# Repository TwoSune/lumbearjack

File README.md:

# Lumbearjack - Ortholinear 60% PCB based on Lumberjack by peej

Lumbearjack is a revision of peej's lumberjack with the following features:
* Pro Micro style controller support
* Per-key RGB and Backlight support
* Rotary encoder support
* SMD diode support
* BSS138 logic level shifter

Lumbearjack is currently designed for the following development boards:
* Helios
* Sea Picro
* Frood
* KB2040 (no encoder support)
  
With support for the following, but you may struggle with external USB data lines
* Liatris
* Elite-Pi

At its core, Lumbearjack remains easy to build with minimal soldering experience, but being familiar with soldering is highly recommended for per-key RGB (SK68XX Mini-E) and backlight (WS2812B 2020).

# Ordering parts

See the [Bill of materials](BOM.md) for a detailed list of the required parts.

PCBs can be manufactuered by a variety of online PCB fabricators. You can use [PCBShopper](https://pcbshopper.com/) to search for the best price.

The [zip file in the gerber directory](https://github.com/peej/lumberjack-keyboard/blob/master/gerber/lumberjack.zip) contains the gerber files your fabricator will need to make the PCB.

When uploading the gerber zip files, use the default PCB settings.

If you want to use a plate, there are [gerbers for FR4 plates](https://github.com/peej/lumberjack-keyboard/tree/smd-usbc/plates/gerbers). For the split plate, you will need two plates, one for each half of the keyboard.

# Construction

First, solder all the diodes on the top of the board. If you do not plan on using an encoder or a switch in the middle, you may omit the diode in the center of the board.
After you solder the diodes, solder the USB port on your board. From there, you may decide whether you would like to solder the LEDs or the controller to your board. It is recommended to solder the controller first so you may test your RGB as you solder them a few at a time.

See [the build guide](guide.md) for more information.

## Need help?

Feel free to create an issue request or contact me via discord at xsune for help!

# Firmware

Firmware is available in my [firmware repository](hyperlink)

Follow the [QMK firmware instructions](https://docs.qmk.fm/#/flashing) to build and flash the firmware.

(as of Rev 1.0, there is no onboard reset button. A reset button will be added to Rev 1.1.) 

## VIAL

Lumbearjack is compatible with Vial. You may follow the instructions for setting up a build environment [here](https://get.vial.today)
ZMK firmware will be added in the future

## Bootloader

 [See the build guide for more information](guide.md#bootloader).

## Matrix information

If you are building your own firmware, the following matrix information will be useful to you:

| Configuration   | Value                                  |
|-----------------|----------------------------------------|
| MATRIX_ROWS     | 12                                      |
| MATRIX_COLS     | 7                                     |
| MATRIX_ROW_PINS | X (GPX), X (GPX), X (GPX), X (GPX), X (GPX), |
| MATRIX_COL_PINS | X (GPX), X (GPX), X (GPX), X (GPX), X (GPX), |
| DIODE_DIRECTION | COL2ROW                                |

Lumbearjack uses an interleaved matrix to save a pin for RGB and a pin for the middle key so KB2040 users may still have access to most of the features. You must use an Elite-C style dev board for encoder support.

# Component cover

Cut a piece of 2mm thick acrylic to size (95x57mm) and drill 4 m2 holes in the corners for the standoffs. Use the PCB or cover.dxf as a guide for the hole positions, you can also use cover.dxf for laser cutting the correct size acrylic.

Affix the 4 standoffs to the PCB with screws from underneath the PCB. Use the remaining 4 screws to attach the acrylic to the top of the standoffs.

# Revisions

## Rev 1.0

* Initial design introduced

## Rev 1.1 plans:
* Make external USB data lines easier to solder for Elite-Pi and Liatris users.
* RGB strip support
* Adjust some LED placements and switch orientations
* Add Reset Button
* Possibly revise the logic level shifter

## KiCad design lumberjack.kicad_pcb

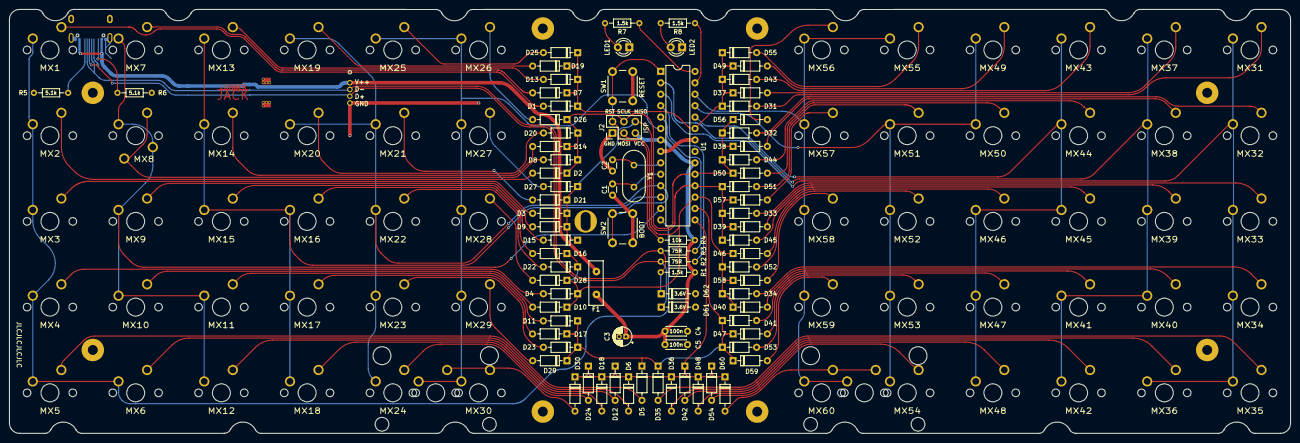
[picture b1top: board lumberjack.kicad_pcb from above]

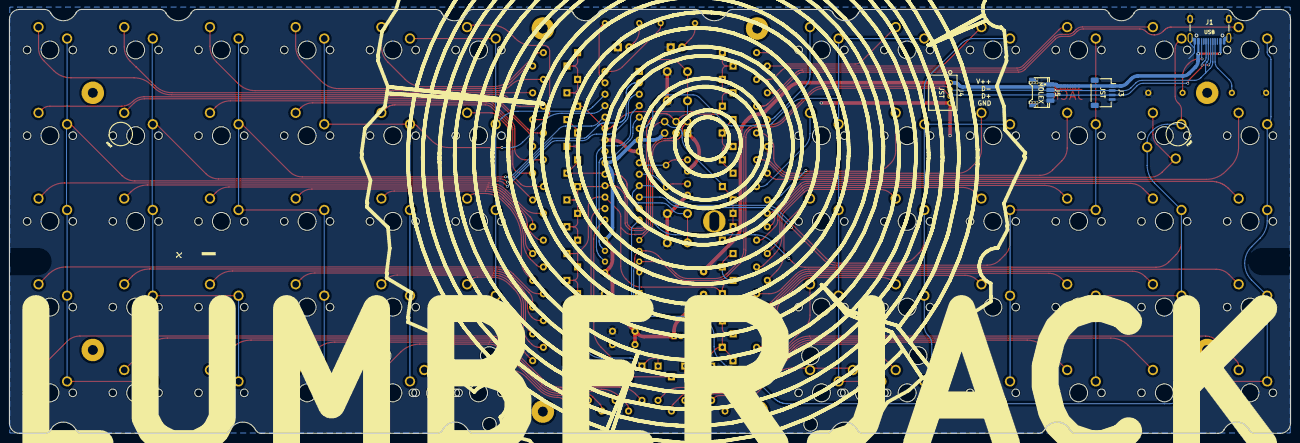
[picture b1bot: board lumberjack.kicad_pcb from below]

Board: 2 copper layers, 284.7 x 94.2 mm, 160 parts (4 on the bottom side), 92 nets.

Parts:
2u_MX30, 2u_MX60: SW_Push; MX_PCB_200B
C1, C2: 22p; C_Disc_D3.0mm_W1.6mm_P2.50mm
C3: 4.7u; CP_Radial_D4.0mm_P1.50mm
C4, C5: 100n; C_Disc_D4.3mm_W1.9mm_P5.00mm
D1, D2, D3, D4, D5, D6, D7, D8, D9, D10, D11, D12, D13, D14, D15, D16, D17, D18, D19, D20, D21, D22, D23, D24, D25, D26, D27, D28, D29, D30, D31, D32, D33, D34, D35, D36, D37, D38, D39, D40, D41, D42, D43, D44, D45, D46, D47, D48, D49, D50, D51, D52, D53, D54, D55, D56, D57, D58, D59, D60: 1N4148; D_DO-35_SOD27_P7.62mm_Horizontal
D61, D62: 3.6V; D_DO-35_SOD27_P7.62mm_Horizontal
F1: 100mA; Fuse_Bourns_MF-RHT100
H1, H2, H3, H4, H8, H9, H10, H11: M2; MountingHole_M2
H5, H6, H7: M2; MountingSlot_M2
J1: USB; TYPE-C-31-M-12
J2: AVR_ISP_6; PinHeader_2x03_P2.54mm_Vertical
J3: JST; JST_SH_SM04B-SRSS-TB_1x04-1MP_P1.00mm_Horizontal
J4: JST; S4B-ZRLFSN
J5: Molex; PicoEZMate-Reinforced-Lite
LED1: RED; LED_D3.0mm
LED2: GREEN; LED_D3.0mm
MX1, MX2, MX3, MX4, MX5, MX6, MX7, MX9, MX10, MX11, MX12, MX13, MX14, MX15, MX16, MX17, MX18, MX19, MX20, MX21, MX22, MX23, MX24, MX25, MX26, MX27, MX28, MX29, MX30, MX31, MX32, MX33, MX34, MX35, MX36, MX37, MX38, MX39, MX40, MX41, MX42, MX43, MX44, MX45, MX46, MX47, MX48, MX49, MX50, MX51, MX52, MX53, MX54, MX55, MX56, MX57, MX58, MX59, MX60: SW_Push; MX
MX8: SW_Push; MX_NTHSTH
R1, R7, R8: 1.5k; R_Axial_DIN0204_L3.6mm_D1.6mm_P7.62mm_Horizontal
R2, R3: 75R; R_Axial_DIN0204_L3.6mm_D1.6mm_P7.62mm_Horizontal
R4: 10k; R_Axial_DIN0204_L3.6mm_D1.6mm_P7.62mm_Horizontal
R5, R6: 5.1k; R_Axial_DIN0204_L3.6mm_D1.6mm_P7.62mm_Horizontal
SW1: RESET; SW_PUSH_6mm
SW2: BOOT; SW_PUSH_6mm
U1: ATMEGA328-PU; DIP-28_W7.62mm
Y1: 16MHz; Crystal_HC49-4H_Vertical

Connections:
+5V: C3.1, C4.1, C5.1, F1.2, J2.5, R1.2, R4.1, U1.7 (VCC), U1.20 (AVCC)
/COL0: MX1.2, MX2.2, MX3.2, MX4.2, MX5.2, MX6.2, U1.14 (PB0)
/COL1: MX7.2, MX8.2, MX9.2, MX10.2, MX11.2, MX12.2, U1.13 (PD7)
/COL2: MX13.2, MX14.2, MX15.2, MX16.2, MX17.2, MX18.2, U1.12 (PD6)
/COL3: MX19.2, MX20.2, MX21.2, MX22.2, MX23.2, MX24.2, SW2.1, U1.11 (PD5)
/COL4: 2u_MX30.2, MX25.2, MX26.2, MX27.2, MX28.2, MX29.2, MX30.2, U1.6 (PD4)
/COL5: MX31.2, MX32.2, MX33.2, MX34.2, MX35.2, MX36.2, U1.3 (PD1)
/COL6: MX37.2, MX38.2, MX39.2, MX40.2, MX41.2, MX42.2, U1.2 (PD0)
/COL7: MX43.2, MX44.2, MX45.2, MX46.2, MX47.2, MX48.2, U1.24 (PC1)
/COL8: MX49.2, MX50.2, MX51.2, MX52.2, MX53.2, MX54.2, U1.25 (PC2)
/COL9: 2u_MX60.2, MX55.2, MX56.2, MX57.2, MX58.2, MX59.2, MX60.2, U1.26 (PC3)
/LED1: R7.1, U1.28 (PC5)
/LED2: R8.1, U1.27 (PC4)
/RESET: J2.2, R4.2, SW1.1, U1.1 (~RESET/PC6)
/ROW0: D1.1 (K), D7.1 (K), D13.1 (K), D19.1 (K), D25.1 (K), D31.1 (K), D37.1 (K), D43.1 (K), D49.1 (K), D55.1 (K), U1.23 (PC0)
/ROW1: D2.1 (K), D8.1 (K), D14.1 (K), D20.1 (K), D26.1 (K), D32.1 (K), D38.1 (K), D44.1 (K), D50.1 (K), D56.1 (K), J2.4, U1.19 (PB5)
/ROW2: D3.1 (K), D9.1 (K), D15.1 (K), D21.1 (K), D27.1 (K), D33.1 (K), D39.1 (K), D45.1 (K), D51.1 (K), D57.1 (K), J2.6, U1.18 (PB4)
/ROW3: D4.1 (K), D10.1 (K), D16.1 (K), D22.1 (K), D28.1 (K), D34.1 (K), D40.1 (K), D46.1 (K), D52.1 (K), D58.1 (K), J2.3, U1.17 (PB3)
/ROW4: D5.1 (K), D11.1 (K), D17.1 (K), D23.1 (K), D29.1 (K), D35.1 (K), D41.1 (K), D47.1 (K), D53.1 (K), D59.1 (K), U1.16 (PB2)
/ROW5: D6.1 (K), D12.1 (K), D18.1 (K), D24.1 (K), D30.1 (K), D36.1 (K), D42.1 (K), D48.1 (K), D54.1 (K), D60.1 (K), U1.15 (PB1)
/USB_D+: R2.2, U1.4 (PD2)
/USB_D-: R3.2, U1.5 (PD3)
GND: C1.2, C2.2, C3.2, C4.2, C5.2, D61.2 (A), D62.2 (A), J1.A1 (GND), J1.B1 (GND), J1.S1 (SHIELD), J2.1, J3.4, J4.1, J5.4, LED1.1 (K), LED2.1 (K), R5.1, R6.1, SW1.2, SW2.2, U1.8 (GND), U1.22 (GND)
unnamed: D1.2 (A), MX1.1
unnamed: D2.2 (A), MX2.1
unnamed: D3.2 (A), MX3.1
unnamed: D4.2 (A), MX4.1
unnamed: D5.2 (A), MX5.1
unnamed: D6.2 (A), MX6.1
unnamed: D7.2 (A), MX7.1
unnamed: D8.2 (A), MX8.1
unnamed: D9.2 (A), MX9.1
unnamed: D10.2 (A), MX10.1
unnamed: D11.2 (A), MX11.1
unnamed: D12.2 (A), MX12.1
unnamed: D13.2 (A), MX13.1
unnamed: D14.2 (A), MX14.1
unnamed: D15.2 (A), MX15.1
unnamed: D16.2 (A), MX16.1
unnamed: D17.2 (A), MX17.1
unnamed: D18.2 (A), MX18.1
unnamed: D19.2 (A), MX19.1
unnamed: D20.2 (A), MX20.1
unnamed: D21.2 (A), MX21.1
unnamed: D22.2 (A), MX22.1
unnamed: D23.2 (A), MX23.1
unnamed: D24.2 (A), MX24.1
unnamed: D25.2 (A), MX25.1
unnamed: D26.2 (A), MX26.1
unnamed: D27.2 (A), MX27.1
unnamed: D28.2 (A), MX28.1
unnamed: D29.2 (A), MX29.1
unnamed: 2u_MX30.1, D30.2 (A), MX30.1
unnamed: D31.2 (A), MX31.1
unnamed: D32.2 (A), MX32.1
unnamed: D33.2 (A), MX33.1
unnamed: D34.2 (A), MX34.1
unnamed: D35.2 (A), MX35.1
unnamed: D36.2 (A), MX36.1
unnamed: D37.2 (A), MX37.1
unnamed: D38.2 (A), MX38.1
unnamed: D39.2 (A), MX39.1
unnamed: D40.2 (A), MX40.1
unnamed: D41.2 (A), MX41.1
unnamed: D42.2 (A), MX42.1
unnamed: D43.2 (A), MX43.1
unnamed: D44.2 (A), MX44.1
unnamed: D45.2 (A), MX45.1
unnamed: D46.2 (A), MX46.1
unnamed: D47.2 (A), MX47.1
unnamed: D48.2 (A), MX48.1
unnamed: D49.2 (A), MX49.1
unnamed: D50.2 (A), MX50.1
unnamed: D51.2 (A), MX51.1
unnamed: D52.2 (A), MX52.1
unnamed: D53.2 (A), MX53.1
unnamed: D54.2 (A), MX54.1
unnamed: D55.2 (A), MX55.1
unnamed: D56.2 (A), MX56.1
unnamed: D57.2 (A), MX57.1
unnamed: D58.2 (A), MX58.1
unnamed: D59.2 (A), MX59.1
unnamed: 2u_MX60.1, D60.2 (A), MX60.1
unnamed: D61.1 (K), J1.A6 (D+), J1.B6 (D+), J3.3, J4.2, J5.3, R2.1
unnamed: D62.1 (K), J1.A7 (D-), J1.B7 (D-), J3.2, J4.3, J5.2, R1.1, R3.1
unnamed: J1.A5 (CC1), R5.2
unnamed: J1.B5 (CC2), R6.2
unnamed: F1.1, J1.A4 (VBUS), J1.B4 (VBUS), J3.1, J4.4, J5.1
unnamed: LED1.2 (A), R7.2
unnamed: LED2.2 (A), R8.2
unnamed: C2.1, U1.9 (XTAL1/PB6), Y1.1
unnamed: C1.1, U1.10 (XTAL2/PB7), Y1.2

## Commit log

2024-04-16 Update gerber files
2024-04-16 Add Molex connector footprint
2024-04-16 Move USB footprint closer to end of board
2024-04-16 Update production bootloader files
2024-04-16 Update documentation
2024-06-26 Add H60 compatible edge cutouts
2025-09-28 Switch to SMD USB-C connector
2025-09-28 Remove top copper layer and fillet traces

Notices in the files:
parts and their libraries:
Copyright 2021 Accelerated Designs. All rights reserved.
